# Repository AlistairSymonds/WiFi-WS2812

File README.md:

# WiFi-WS2812
A collection of code designed around an ESP8266 and a Teensy 3.2 for various remote controlled LED lighting effects

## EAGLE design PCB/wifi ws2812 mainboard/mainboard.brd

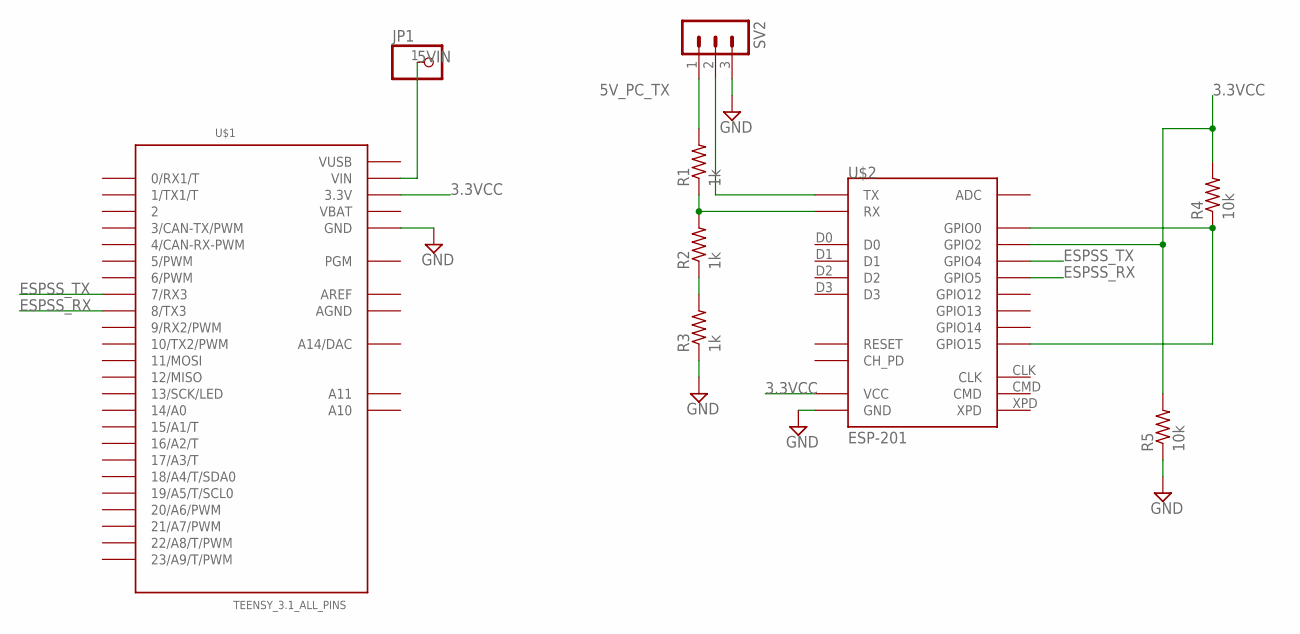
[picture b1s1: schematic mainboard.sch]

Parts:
JP1: PINHD-1X1; 1X01
R1, R2, R3: 1k; 0207/7
R4, R5: 10k; 0207/7
SV2: MA03-1
U$1: TEENSY_3.1_ALL_PINS; TEENSY3-ALL_PINS
U$2: ESP-201

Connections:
3.3VCC: R4.2, R5.2, U$1.3.3V, U$1.3.3V1 (3.3V), U$2.3V3 (VCC), U$2.3V3_2 (VCC), U$2.3V3_3 (VCC), U$2.GPIO2
5VIN: JP1.1, U$1.VIN
5V_PC_TX: R1.2, SV2.1
AGND: U$1.AGND
AREF: U$1.AREF
ESPSS_RX: U$1.8 (8/TX3), U$2.GPIO5
ESPSS_TX: U$1.7 (7/RX3), U$2.GPIO4
GND: R3.1, R5.1, SV2.3, U$1.GND, U$1.GND1 (GND), U$2.GND, U$2.GND_2 (GND), U$2.GND_3 (GND)
unnamed: R1.1, R2.2, U$2.RX
unnamed: SV2.2, U$2.TX
unnamed: R4.1, U$2.GPIO0, U$2.GPIO15
unnamed: R2.1, R3.2
VBAT: U$1.VBAT
VUSB: U$1.VUSB

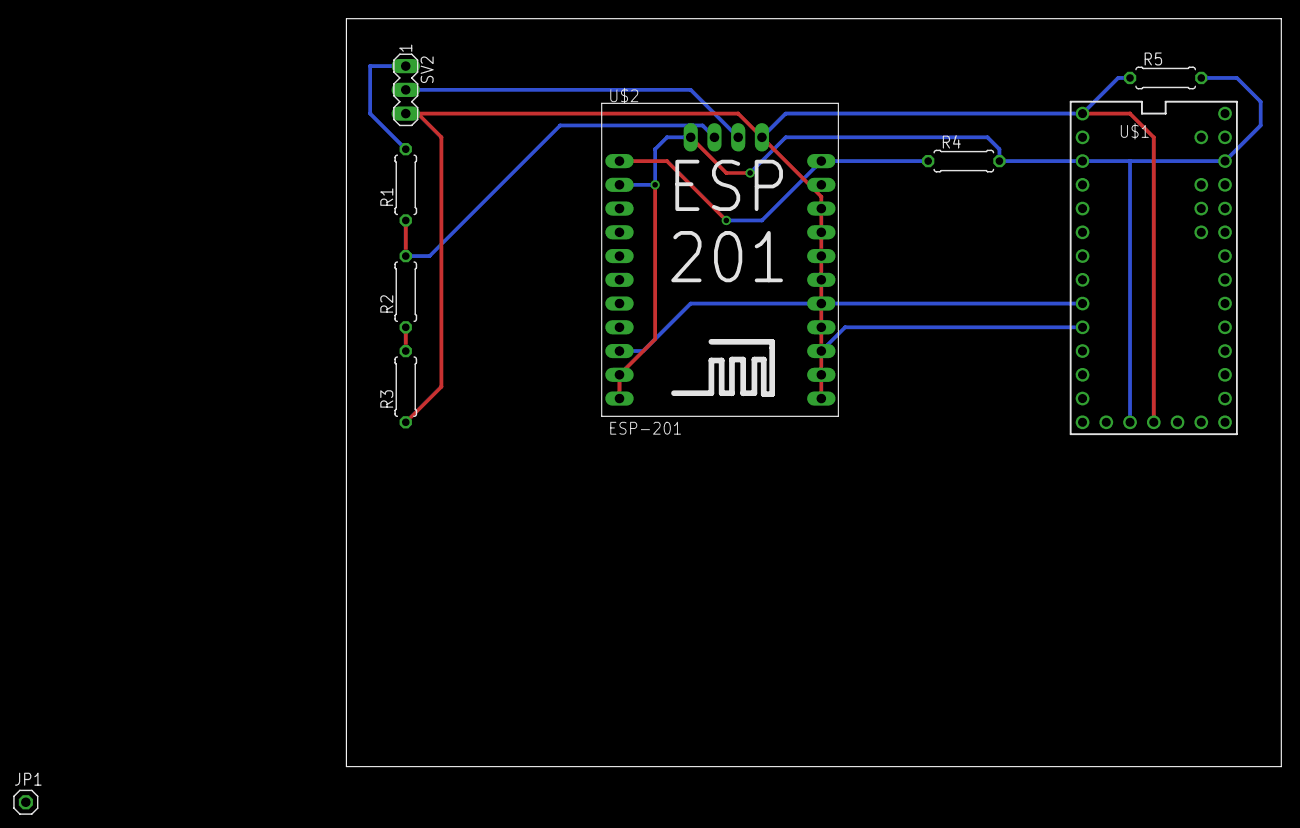
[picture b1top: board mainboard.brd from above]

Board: 2 copper layers, 100.0 x 80.0 mm, 9 parts (0 on the bottom side), 10 nets.

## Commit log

2016-06-09 Serial Control Proof of Concept
    Proof of concept over USB into an Arduino
2016-06-12 Added a list of pid and modifier descriptions
2016-06-19 Updating code to make it more modular and adding more animations
2016-06-21 new file: .gitignore renamed: SerialControl/SerialControl.ino -> Code/SerialControl_Uno/SerialControl_Uno.ino new file: PCB/wifi ws2812 mainboard/eagle-TOWER.epf new file: PCB/wifi ws2812 mainboard/e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
2016-06-28 new file: Code/Java Desktop/WiFi-Home-Java/.classpath new file: Code/Java Desktop/WiFi-Home-Java/.gitignore new file: Code/Java Desktop/WiFi-Home-Java/.project new file: Code/Java Desktop/WiFi-Home-J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
2016-07-29 gui update
2016-07-29 tidying up
2016-08-22 Functional Prototype
2016-09-03 Basic Android App
2017-02-05 OctoWS Testing
2017-04-02 cleaning out PCB realted files
2017-04-06 Added changed output to OCTO
    Reordered header files to change output mode to octo
2017-04-06 Ignoring PCB rubbish, but for real
2017-04-06 PCB DELTED!
    it wasn't being used
2017-04-06 Restructure to just code
